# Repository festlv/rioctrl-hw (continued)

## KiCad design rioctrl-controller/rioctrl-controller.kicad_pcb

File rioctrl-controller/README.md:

# rioctrl-controller

The heart of controller is Lattice ECP5-series FPGA with 25k logic cells.

It has the following inputs/outputs:

* RJ45 Ethernet interface to PC (via Wiznet W5500)
* USB TypeC for re-flashing the FPGA (using RP2040 microcontroller with [pico-dirtyJtag](https://github.com/phdussud/pico-dirtyJtag) firmware)
* 12-24V DC input for powering the FPGA and basic slot hardware
* E-Stop signal that inhibits slot outputs in hardware, independant of FPGA gateware
* PMOD header for future expansion (e.g. controlling the board via SPI from RaspberryPi or something)
* JTAG header for FPGA debugging
* SWD header for JTAG probe debugging :)
* Six 2x13 pin 2.54mm sockets for slots (each has 12 FPGA signals, additional shared enable signal, +3.3V, +5V and input DC power)

Slot specification:
* Preferred slot PCB size: 100x100mm
* There are 12 FPGA signals wired to each slot, all of them are 3.3V.
* The following power rails are wired to each slot:
  * 3.3V
  * 5V
  * Input DC (12-24V)
* Each slot has an enable signal, whose state is a logical AND of FPGA enable output (watchdog-protected when using riocore) and external EStop input.
* Each slot **MUST** inhibit it's outputs in hardware when the enable signal is low.

# Changelog

## V1.0 -> V1.1
* Fix Y1 orientation
* DNP the USB VBUS -> 5V diode (it's useless, as 3.3V rails are generated by input voltage)
* Change LED:OK to green
 
# Bringup notes

* Build and flash the default configuration of pico-dirtyJtag (hold the boot button while turning on 12V power, then connect USB and flash via copying .uf2 to removable drive).
* Try to see if the FPGA is detected:
```
$ openFPGALoader -c dirtyJtag --detect

Jtag frequency : requested 6000000Hz -> real 6000000Hz
index 0:
	idcode 0x41111043
	manufacturer lattice
	family ECP5
	model  LFE5U-25
	irlength 8
```

# Version 1.0 rework
* Y1 needs to be rotated 90 degrees (again, sigh)
* Remove the D9 diode (USB power does not work anyway)
* Change D12 to green LED

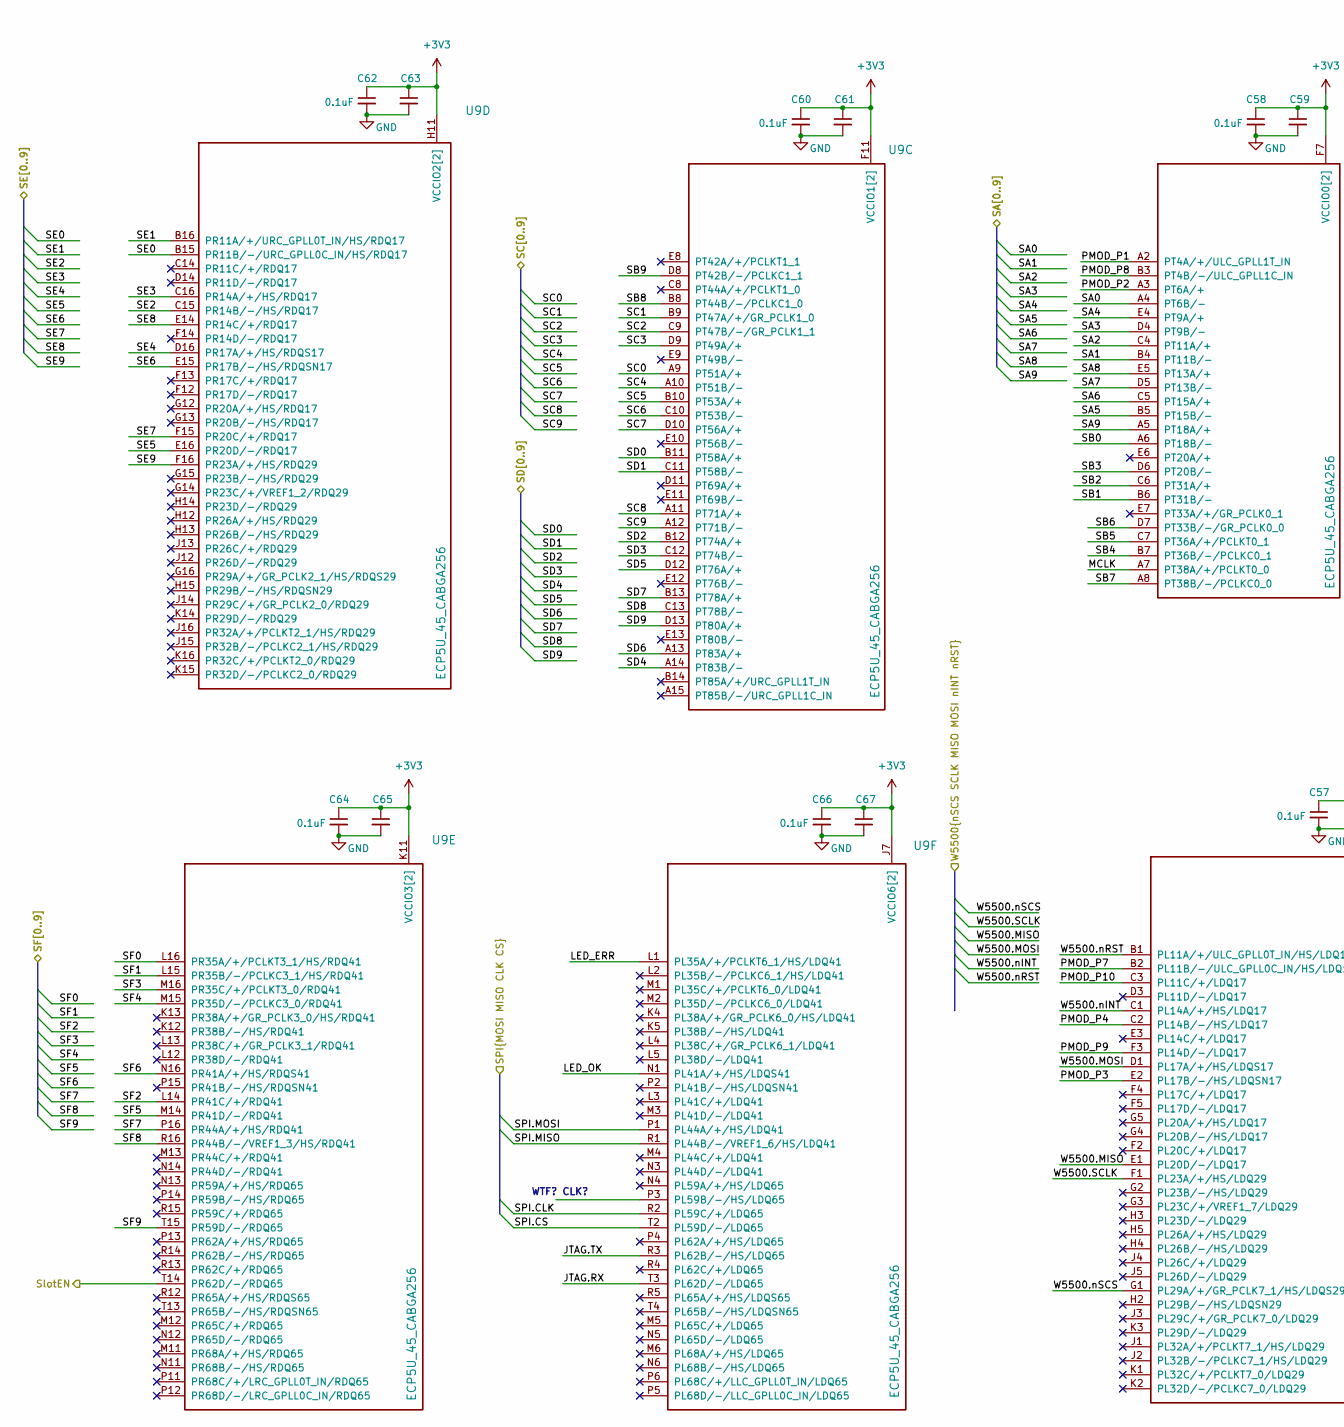
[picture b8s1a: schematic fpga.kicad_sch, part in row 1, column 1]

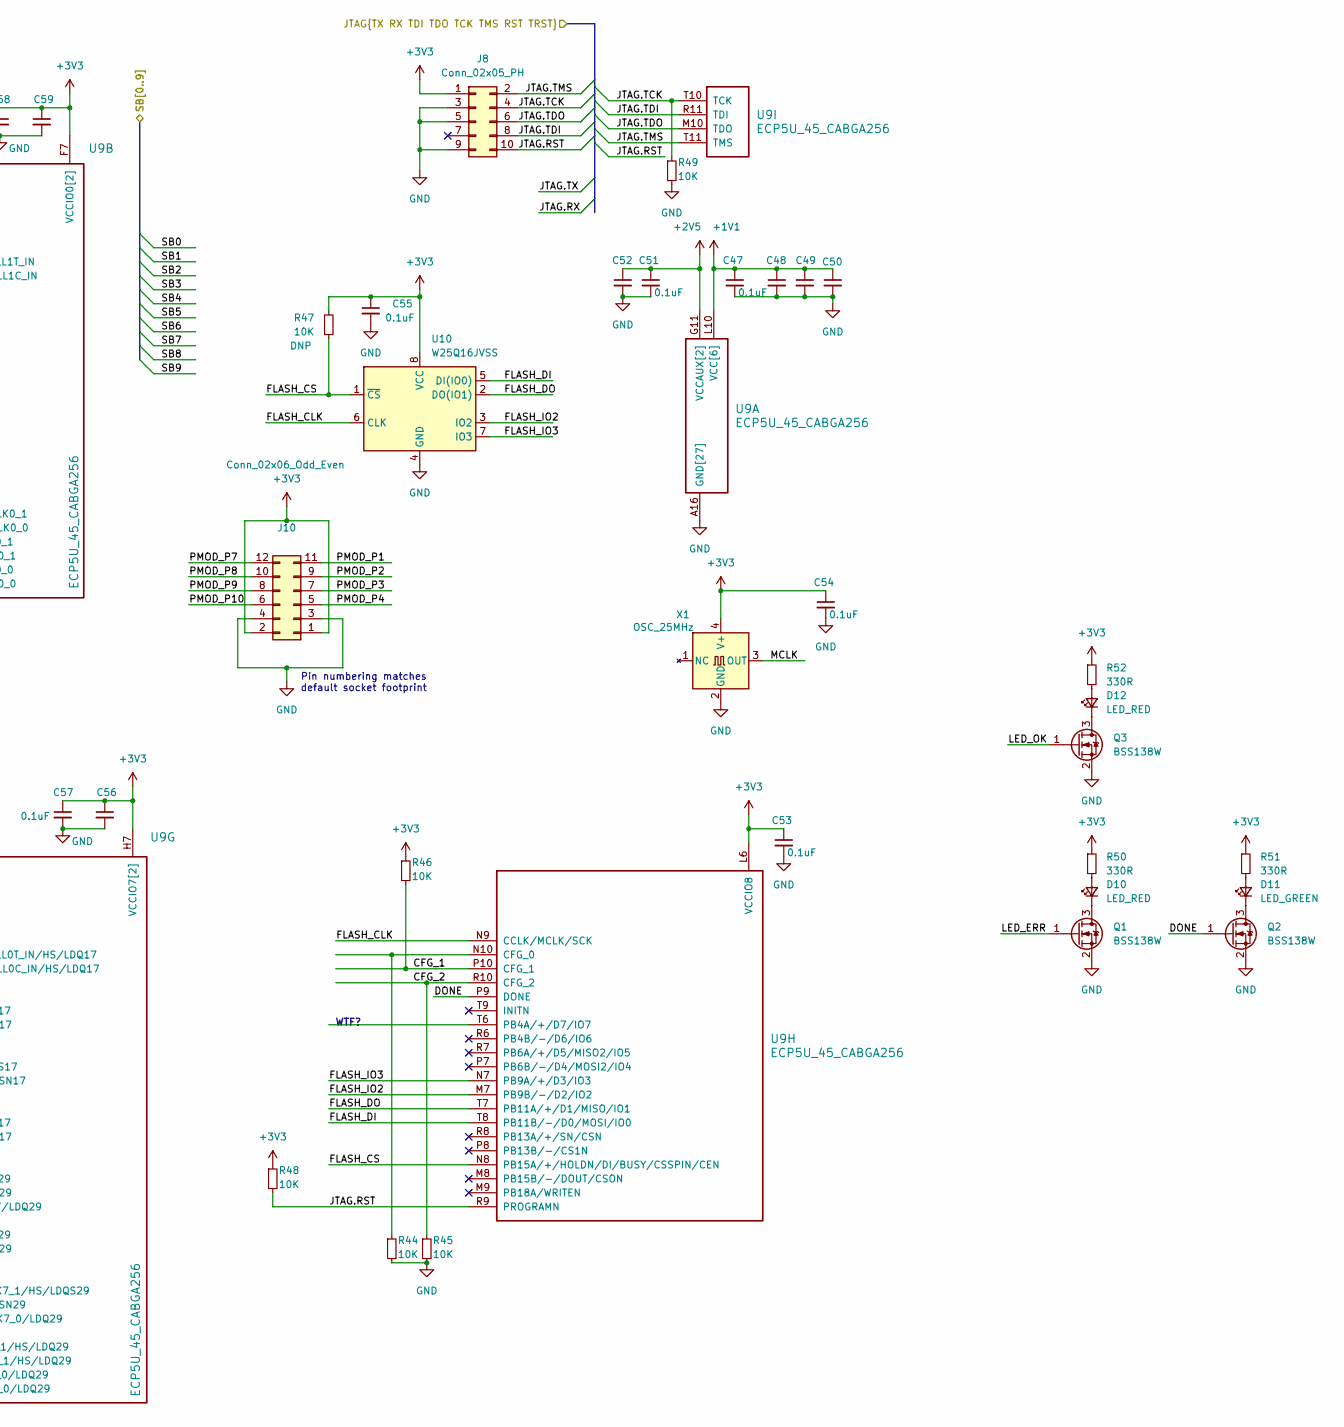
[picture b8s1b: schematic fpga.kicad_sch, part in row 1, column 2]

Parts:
C47, C48, C49, C50, C51, C52, C53, C54, C56, C57, C58, C59, C60, C61, C62, C63, C64, C65, C66, C67: 0.1uF; C_0402_1005Metric
C55: 0.1uF; C_0603_1608Metric; MPN CC0603KRX7R9BB104; LCSC# C14663
D10, D12: LED_RED; LED_0603_1608Metric; MPN SZYY0603R; LCSC# C434419
D11: LED_GREEN; LED_0603_1608Metric; MPN SZYY0603YG; LCSC# C434423
J8: Conn_02x05_PH; IDC-Header_2x05_P2.54mm_Vertical
J10: Conn_02x06_Odd_Even; PinSocket_2x06_P2.54mm_Horizontal
Q1, Q2, Q3: BSS138W; SOT-323_SC-70; MPN BSS138W; LCSC# C504052
R44, R45, R46, R48, R49: 10K; R_0603_1608Metric
R47: 10K; R_0603_1608Metric; MPN RC0603FR-0710KL; LCSC# C98220
R50, R51, R52: 330R; R_0603_1608Metric
U9: ECP5U_45_CABGA256; BGA-256_14.0x14.0mm_Layout16x16_P0.8mm_Ball0.45mm_Pad0.32mm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; MPN LFE5U-12F-6BG256C
U10: W25Q16JVSS; SOIC-8_5.23x5.23mm_P1.27mm; MPN W25Q16JVSSIQ; LCSC# C82317
X1: OSC_25MHz; Oscillator_SMD_EuroQuartz_XO32-4Pin_3.2x2.5mm; MPN OT322525MJBA4SL; LCSC# C669088

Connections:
+1V1: C47.1, C48.1, C49.1, C50.1, U9.G6 (VCC[6]), U9.G7 (VCC[6]), U9.G9 (VCC[6]), U9.L8 (VCC[6]), U9.L9 (VCC[6]), U9.L10 (VCC[6]); also elsewhere on the board
+2V5: C51.1, C52.1, U9.G11 (VCCAUX[2]), U9.L7 (VCCAUX[2]); also elsewhere on the board
+3V3: C53.1, C54.1, C55.1, C56.1, C57.1, C58.1, C59.1, C60.1, C61.1, C62.1, C63.1, C64.1, C65.1, C66.1, C67.1, J8.1, J10.1, J10.2, R46.1, R47.2, R48.1, R50.1, R51.1, R52.1, U9.F6 (VCCIO0[2]), U9.F7 (VCCIO0[2]), U9.F10 (VCCIO1[2]), U9.F11 (VCCIO1[2]), U9.H6 (VCCIO7[2]), U9.H7 (VCCIO7[2]), U9.H11 (VCCIO2[2]), U9.J6 (VCCIO6[2]), U9.J7 (VCCIO6[2]), U9.J11 (VCCIO2[2]), U9.K11 (VCCIO3[2]), U9.L6 (VCCIO8), U9.L11 (VCCIO3[2]), U10.8 (VCC), X1.4 (V+); also elsewhere on the board
/FPGA/CFG_1: R46.2, U9.P10 (CFG_1)
/FPGA/CFG_2: R45.1, U9.R10 (CFG_2)
/FPGA/DONE: Q2.1 (G), U9.P9 (DONE)
/FPGA/FLASH_CLK: U9.N9 (CCLK/MCLK/SCK), U10.6 (CLK)
/FPGA/FLASH_CS: R47.1, U9.N8 (PB15A/+/HOLDN/DI/BUSY/CSSPIN/CEN), U10.1 (~CS)
/FPGA/FLASH_DI: U9.T8 (PB11B/-/D0/MOSI/IO0), U10.5 (DI(IO0))
/FPGA/FLASH_DO: U9.T7 (PB11A/+/D1/MISO/IO1), U10.2 (DO(IO1))
/FPGA/FLASH_IO2: U9.M7 (PB9B/-/D2/IO2), U10.3 (IO2)
/FPGA/FLASH_IO3: U9.N7 (PB9A/+/D3/IO3), U10.7 (IO3)
/FPGA/LED_ERR: Q1.1 (G), U9.L1 (PL35A/+/PCLKT6_1/HS/LDQ41)
/FPGA/LED_OK: Q3.1 (G), U9.N1 (PL41A/+/HS/LDQS41)
/FPGA/MCLK: U9.A7 (PT38A/+/PCLKT0_0), X1.3 (OUT)
/FPGA/PMOD_P1: J10.11, U9.A2 (PT4A/+/ULC_GPLL1T_IN)
/FPGA/PMOD_P2: J10.9, U9.A3 (PT6A/+)
/FPGA/PMOD_P3: J10.7, U9.E2 (PL17B/-/HS/LDQSN17)
/FPGA/PMOD_P4: J10.5, U9.C2 (PL14B/-/HS/LDQ17)
/FPGA/PMOD_P7: J10.12, U9.B2 (PL11B/-/ULC_GPLL0C_IN/HS/LDQ17)
/FPGA/PMOD_P8: J10.10, U9.B3 (PT4B/-/ULC_GPLL1C_IN)
/FPGA/PMOD_P9: J10.8, U9.F3 (PL14D/-/LDQ17)
/FPGA/PMOD_P10: J10.6, U9.C3 (PL11C/+/LDQ17)
/FPGA/SA0: U9.A4 (PT6B/-); also elsewhere on the board
/FPGA/SA1: U9.B4 (PT11B/-); also elsewhere on the board
/FPGA/SA2: U9.C4 (PT11A/+); also elsewhere on the board
/FPGA/SA3: U9.D4 (PT9B/-); also elsewhere on the board
/FPGA/SA4: U9.E4 (PT9A/+); also elsewhere on the board
/FPGA/SA5: U9.B5 (PT15B/-); also elsewhere on the board
/FPGA/SA6: U9.C5 (PT15A/+); also elsewhere on the board
/FPGA/SA7: U9.D5 (PT13B/-); also elsewhere on the board
/FPGA/SA8: U9.E5 (PT13A/+); also elsewhere on the board
/FPGA/SA9: U9.A5 (PT18A/+); also elsewhere on the board
/FPGA/SB0: U9.A6 (PT18B/-); also elsewhere on the board
/FPGA/SB1: U9.B6 (PT31B/-); also elsewhere on the board
/FPGA/SB2: U9.C6 (PT31A/+); also elsewhere on the board
/FPGA/SB3: U9.D6 (PT20B/-); also elsewhere on the board
/FPGA/SB4: U9.B7 (PT36B/-/PCLKC0_1); also elsewhere on the board
/FPGA/SB5: U9.C7 (PT36A/+/PCLKT0_1); also elsewhere on the board
/FPGA/SB6: U9.D7 (PT33B/-/GR_PCLK0_0); also elsewhere on the board
/FPGA/SB7: U9.A8 (PT38B/-/PCLKC0_0); also elsewhere on the board
/FPGA/SB8: U9.B8 (PT44B/-/PCLKC1_0); also elsewhere on the board
/FPGA/SB9: U9.D8 (PT42B/-/PCLKC1_1); also elsewhere on the board
/FPGA/SC0: U9.A9 (PT51A/+); also elsewhere on the board
/FPGA/SC1: U9.B9 (PT47A/+/GR_PCLK1_0); also elsewhere on the board
/FPGA/SC2: U9.C9 (PT47B/-/GR_PCLK1_1); also elsewhere on the board
/FPGA/SC3: U9.D9 (PT49A/+); also elsewhere on the board
/FPGA/SC4: U9.A10 (PT51B/-); also elsewhere on the board
/FPGA/SC5: U9.B10 (PT53A/+); also elsewhere on the board
/FPGA/SC6: U9.C10 (PT53B/-); also elsewhere on the board
/FPGA/SC7: U9.D10 (PT56A/+); also elsewhere on the board
/FPGA/SC8: U9.A11 (PT71A/+); also elsewhere on the board
/FPGA/SC9: U9.A12 (PT71B/-); also elsewhere on the board
/FPGA/SD0: U9.B11 (PT58A/+); also elsewhere on the board
/FPGA/SD1: U9.C11 (PT58B/-); also elsewhere on the board
/FPGA/SD2: U9.B12 (PT74A/+); also elsewhere on the board
/FPGA/SD3: U9.C12 (PT74B/-); also elsewhere on the board
/FPGA/SD4: U9.A14 (PT83B/-); also elsewhere on the board
/FPGA/SD5: U9.D12 (PT76A/+); also elsewhere on the board
/FPGA/SD6: U9.A13 (PT83A/+); also elsewhere on the board
/FPGA/SD7: U9.B13 (PT78A/+); also elsewhere on the board
/FPGA/SD8: U9.C13 (PT78B/-); also elsewhere on the board
/FPGA/SD9: U9.D13 (PT80A/+); also elsewhere on the board
/FPGA/SE0: U9.B15 (PR11B/-/URC_GPLL0C_IN/HS/RDQ17); also elsewhere on the board
/FPGA/SE1: U9.B16 (PR11A/+/URC_GPLL0T_IN/HS/RDQ17); also elsewhere on the board
/FPGA/SE2: U9.C15 (PR14B/-/HS/RDQ17); also elsewhere on the board
/FPGA/SE3: U9.C16 (PR14A/+/HS/RDQ17); also elsewhere on the board
/FPGA/SE4: U9.D16 (PR17A/+/HS/RDQS17); also elsewhere on the board
/FPGA/SE5: U9.E16 (PR20D/-/RDQ17); also elsewhere on the board
/FPGA/SE6: U9.E15 (PR17B/-/HS/RDQSN17); also elsewhere on the board
/FPGA/SE7: U9.F15 (PR20C/+/RDQ17); also elsewhere on the board
/FPGA/SE8: U9.E14 (PR14C/+/RDQ17); also elsewhere on the board
/FPGA/SE9: U9.F16 (PR23A/+/HS/RDQ29); also elsewhere on the board
/FPGA/SF0: U9.L16 (PR35A/+/PCLKT3_1/HS/RDQ41); also elsewhere on the board
/FPGA/SF1: U9.L15 (PR35B/-/PCLKC3_1/HS/RDQ41); also elsewhere on the board
/FPGA/SF2: U9.L14 (PR41C/+/RDQ41); also elsewhere on the board
/FPGA/SF3: U9.M16 (PR35C/+/PCLKT3_0/RDQ41); also elsewhere on the board
/FPGA/SF4: U9.M15 (PR35D/-/PCLKC3_0/RDQ41); also elsewhere on the board
/FPGA/SF5: U9.M14 (PR41D/-/RDQ41); also elsewhere on the board
/FPGA/SF6: U9.N16 (PR41A/+/HS/RDQS41); also elsewhere on the board
/FPGA/SF7: U9.P16 (PR44A/+/HS/RDQ41); also elsewhere on the board
/FPGA/SF8: U9.R16 (PR44B/-/VREF1_3/HS/RDQ41); also elsewhere on the board
/FPGA/SF9: U9.T15 (PR59D/-/RDQ65); also elsewhere on the board
/FPGA/SPI.CLK: U9.R2 (PL59C/+/LDQ65); also elsewhere on the board
/FPGA/SPI.CS: U9.T2 (PL59D/-/LDQ65); also elsewhere on the board
/FPGA/SPI.MISO: U9.R1 (PL44B/-/VREF1_6/HS/LDQ41); also elsewhere on the board
/FPGA/SPI.MOSI: U9.P1 (PL44A/+/HS/LDQ41); also elsewhere on the board
/FPGA/W5500.MISO: U9.E1 (PL20D/-/LDQ17); also elsewhere on the board
/FPGA/W5500.MOSI: U9.D1 (PL17A/+/HS/LDQS17); also elsewhere on the board
/FPGA/W5500.SCLK: U9.F1 (PL23A/+/HS/LDQ29); also elsewhere on the board
/FPGA/W5500.nINT: U9.C1 (PL14A/+/HS/LDQ17); also elsewhere on the board
/FPGA/W5500.nRST: U9.B1 (PL11A/+/ULC_GPLL0T_IN/HS/LDQ17); also elsewhere on the board
/FPGA/W5500.nSCS: U9.G1 (PL29A/+/GR_PCLK7_1/HS/LDQS29); also elsewhere on the board
/RP2040 JTAG/JTAG.RST: J8.10, R48.2, U9.R9 (PROGRAMN); also elsewhere on the board
/RP2040 JTAG/JTAG.RX: U9.T3 (PL62D/-/LDQ65); also elsewhere on the board
/RP2040 JTAG/JTAG.TCK: J8.4, R49.1, U9.T10 (TCK); also elsewhere on the board
/RP2040 JTAG/JTAG.TDI: J8.8, U9.R11 (TDI); also elsewhere on the board
/RP2040 JTAG/JTAG.TDO: J8.6, U9.M10 (TDO); also elsewhere on the board
/RP2040 JTAG/JTAG.TMS: J8.2, U9.T11 (TMS); also elsewhere on the board
/RP2040 JTAG/JTAG.TX: U9.R3 (PL62B/-/HS/LDQ65); also elsewhere on the board
/Slots/SlotEN: U9.T14 (PR62D/-/RDQ65); also elsewhere on the board
GND: C47.2, C48.2, C49.2, C50.2, C51.2, C52.2, C53.2, C54.2, C55.2, C56.2, C57.2, C58.2, C59.2, C60.2, C61.2, C62.2, C63.2, C64.2, C65.2, C66.2, C67.2, J8.3, J8.5, J8.9, J10.3, J10.4, Q1.2 (S), Q2.2 (S), Q3.2 (S), R44.2, R45.2, R49.2, U9.A1 (GND[27]), U9.A16 (GND[27]), U9.D2 (GND[27]), U9.D15 (GND[27]), U9.F8 (GND[27]), U9.F9 (GND[27]), U9.G8 (GND[27]), U9.G10 (GND[27]), U9.H1 (GND[27]), U9.H8 (GND[27]), U9.H9 (GND[27]), U9.H10 (GND[27]), U9.H16 (GND[27]), U9.J8 (GND[27]), U9.J9 (GND[27]), U9.J10 (GND[27]), U9.K6 (GND[27]), U9.K7 (GND[27]), U9.K8 (GND[27]), U9.K9 (GND[27]), U9.K10 (GND[27]), U9.N2 (GND[27]), U9.N15 (GND[27]), U9.T1 (GND[27]), U9.T5 (GND[27]), U9.T12 (GND[27]), U9.T16 (GND[27]), U10.4 (GND), X1.2 (GND); also elsewhere on the board
unnamed: D10.2 (A), R50.2
unnamed: D10.1 (K), Q1.3 (D)
unnamed: D11.2 (A), R51.2
unnamed: D11.1 (K), Q2.3 (D)
unnamed: D12.2 (A), R52.2
unnamed: D12.1 (K), Q3.3 (D)
unnamed: R44.1, U9.N10 (CFG_0)

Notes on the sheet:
WTF?
WTF? CLK?
Pin numbering matches default socket footprint

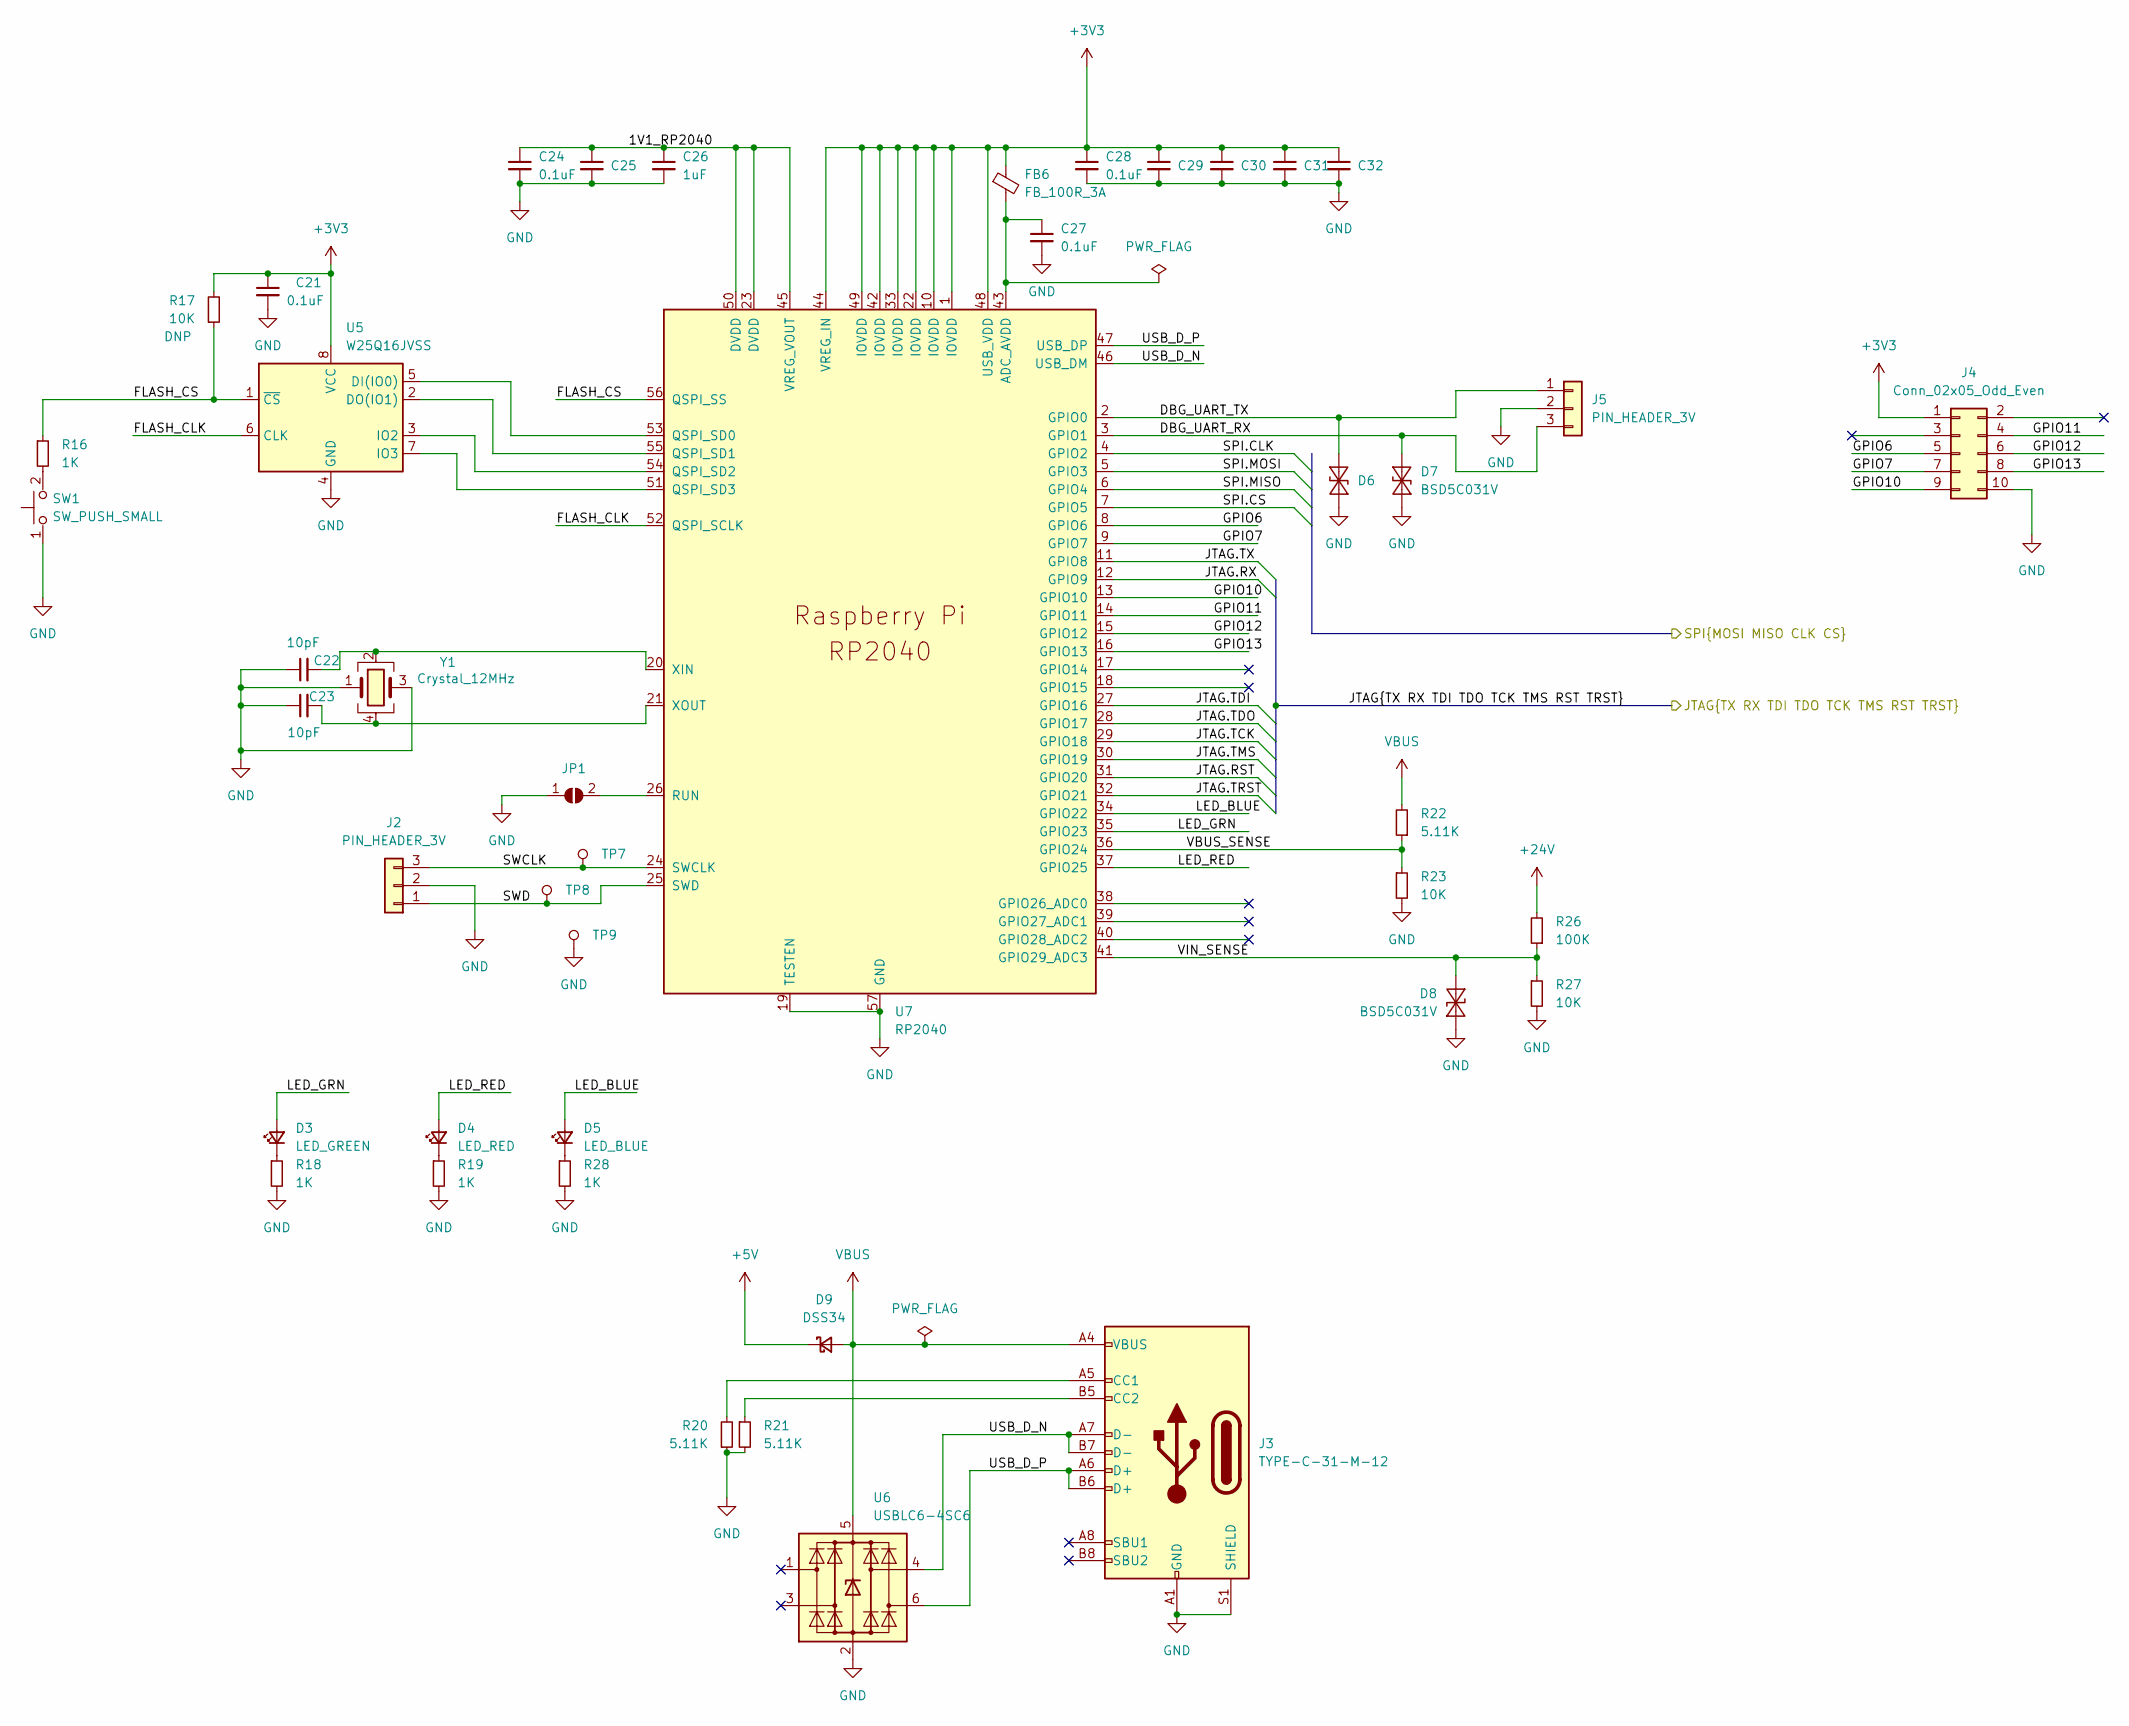
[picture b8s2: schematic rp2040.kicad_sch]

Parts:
C21, C24, C25, C27, C28, C29, C30, C31, C32: 0.1uF; C_0603_1608Metric; MPN CC0603KRX7R9BB104; LCSC# C14663
C22, C23: 10pF; C_0603_1608Metric; MPN CC0603JRNPO9BN100; LCSC# C106245
C26: 1uF; C_0603_1608Metric; MPN CL10A105KA8NNNC; LCSC# C5673
D3: LED_GREEN; LED_0603_1608Metric; MPN SZYY0603YG; LCSC# C434423
D4: LED_RED; LED_0603_1608Metric; MPN SZYY0603R; LCSC# C434419
D5: LED_BLUE; LED_0603_1608Metric; MPN XL-1608UBC-04; LCSC# C965807
D6, D7, D8: BSD5C031V; D_SOD-523; MPN BSD5C031V; LCSC# C151984
D9: DSS34; D_SOD-123F; MPN DSS34; LCSC# C511866
FB6: FB_100R_3A; L_0603_1608Metric; MPN UPZ1608E101-3R0TF; LCSC# C96995
J2, J5: PIN_HEADER_3V; PinHeader_1x03_P2.54mm_Vertical; MPN C49257; LCSC# C49257
J3: TYPE-C-31-M-12; USB_C_Receptacle_HRO_TYPE-C-31-M-12; MPN TYPE-C-31-M-12; LCSC# C165948
J4: Conn_02x05_Odd_Even; PinHeader_2x05_P2.54mm_Vertical
JP1: SolderJumper_2_Open; SolderJumper-2_P1.3mm_Open_RoundedPad1.0x1.5mm
R16, R18, R19, R28: 1K; R_0603_1608Metric; MPN RC0603FR-071KL; LCSC# C22548
R17, R23, R27: 10K; R_0603_1608Metric; MPN RC0603FR-0710KL; LCSC# C98220
R20, R21, R22: 5.11K; R_0603_1608Metric; MPN RC0603FR-075K11L; LCSC# C112314
R26: 100K; R_0603_1608Metric; MPN RC0603FR-075K11L; LCSC# C112314
SW1: SW_PUSH_SMALL; SW_SPST_AR02016; MPN TS-1088-AR02016; LCSC# C720477
TP7, TP8, TP9: TP_1MM; TestPoint_Pad_D1.0mm
U5: W25Q16JVSS; SOIC-8_5.23x5.23mm_P1.27mm; MPN W25Q16JVSSIQ; LCSC# C82317
U6: USBLC6-4SC6; SOT-23-6; MPN USBLC6-4SC6; LCSC# C5197386
U7: RP2040; RP2040-QFN-56; MPN RP2040; LCSC# C2040
Y1: Crystal_12MHz; Crystal_SMD_2520-4Pin_2.5x2.0mm; MPN TXM12M0004252DBCEO00T; LCSC# C284154

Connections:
+3V3: C21.1, C28.1, C29.1, C30.1, C31.1, C32.1, FB6.1, J4.1, R17.2, U5.8 (VCC), U7.1 (IOVDD), U7.10 (IOVDD), U7.22 (IOVDD), U7.33 (IOVDD), U7.42 (IOVDD), U7.44 (VREG_IN), U7.48 (USB_VDD), U7.49 (IOVDD); also elsewhere on the board
+5V: D9.1 (K); also elsewhere on the board
+24V: R26.2; also elsewhere on the board
/FPGA/SPI.CLK: U7.4 (GPIO2); also elsewhere on the board
/FPGA/SPI.CS: U7.7 (GPIO5); also elsewhere on the board
/FPGA/SPI.MISO: U7.6 (GPIO4); also elsewhere on the board
/FPGA/SPI.MOSI: U7.5 (GPIO3); also elsewhere on the board
/RP2040 JTAG/1V1_RP2040: C24.1, C25.1, C26.1, U7.23 (DVDD), U7.45 (VREG_VOUT), U7.50 (DVDD)
/RP2040 JTAG/DBG_UART_RX: D7.2 (A2), J5.3, U7.3 (GPIO1)
/RP2040 JTAG/DBG_UART_TX: D6.2 (A2), J5.1, U7.2 (GPIO0)
/RP2040 JTAG/FLASH_CLK: U5.6 (CLK), U7.52 (QSPI_SCLK)
/RP2040 JTAG/FLASH_CS: R16.1, R17.1, U5.1 (~CS), U7.56 (QSPI_SS)
/RP2040 JTAG/GPIO6: J4.5, U7.8 (GPIO6)
/RP2040 JTAG/GPIO7: J4.7, U7.9 (GPIO7)
/RP2040 JTAG/GPIO10: J4.9, U7.13 (GPIO10)
/RP2040 JTAG/GPIO11: J4.4, U7.14 (GPIO11)
/RP2040 JTAG/GPIO12: J4.6, U7.15 (GPIO12)
/RP2040 JTAG/GPIO13: J4.8, U7.16 (GPIO13)
/RP2040 JTAG/JTAG.RST: U7.31 (GPIO20); also elsewhere on the board
/RP2040 JTAG/JTAG.RX: U7.12 (GPIO9); also elsewhere on the board
/RP2040 JTAG/JTAG.TCK: U7.29 (GPIO18); also elsewhere on the board
/RP2040 JTAG/JTAG.TDI: U7.27 (GPIO16); also elsewhere on the board
/RP2040 JTAG/JTAG.TDO: U7.28 (GPIO17); also elsewhere on the board
/RP2040 JTAG/JTAG.TMS: U7.30 (GPIO19); also elsewhere on the board
/RP2040 JTAG/JTAG.TRST: U7.32 (GPIO21)
/RP2040 JTAG/JTAG.TX: U7.11 (GPIO8); also elsewhere on the board
/RP2040 JTAG/LED_BLUE: D5.2 (A), U7.34 (GPIO22)
/RP2040 JTAG/LED_GRN: D3.2 (A), U7.35 (GPIO23)
/RP2040 JTAG/LED_RED: D4.2 (A), U7.37 (GPIO25)
/RP2040 JTAG/SWCLK: J2.3, TP7.1, U7.24 (SWCLK)
/RP2040 JTAG/SWD: J2.1, TP8.1, U7.25 (SWD)
/RP2040 JTAG/USB_D_N: J3.A7 (D-), J3.B7 (D-), U6.4 (I/O3), U7.46 (USB_DM)
/RP2040 JTAG/USB_D_P: J3.A6 (D+), J3.B6 (D+), U6.6 (I/O4), U7.47 (USB_DP)
/RP2040 JTAG/VBUS_SENSE: R22.1, R23.1, U7.36 (GPIO24)
/RP2040 JTAG/VIN_SENSE: D8.2 (A2), R26.1, R27.1, U7.41 (GPIO29_ADC3)
GND: C21.2, C22.1, C23.1, C24.2, C25.2, C26.2, C27.2, C28.2, C29.2, C30.2, C31.2, C32.2, D6.1 (A1), D7.1 (A1), D8.1 (A1), J2.2, J3.A1 (GND), J3.A12 (GND), J3.B1 (GND), J3.B12 (GND), J3.S1 (SHIELD), J4.10, J5.2, JP1.1 (A), R18.2, R19.2, R20.1, R21.2, R23.2, R27.2, R28.2, SW1.1, TP9.1, U5.4 (GND), U6.2 (GND), U7.19 (TESTEN), U7.57 (GND), Y1.1, Y1.3; also elsewhere on the board
unnamed: D3.1 (K), R18.1
unnamed: D4.1 (K), R19.1
unnamed: D5.1 (K), R28.1
unnamed: J3.A5 (CC1), R20.2
unnamed: J3.B5 (CC2), R21.1
unnamed: JP1.2 (B), U7.26 (RUN)
unnamed: R16.2, SW1.2 (A)
unnamed: U5.5 (DI(IO0)), U7.53 (QSPI_SD0)
unnamed: U5.2 (DO(IO1)), U7.55 (QSPI_SD1)
unnamed: U5.3 (IO2), U7.54 (QSPI_SD2)
unnamed: U5.7 (IO3), U7.51 (QSPI_SD3)
unnamed: C27.1, FB6.2, U7.43 (ADC_AVDD)
unnamed: C22.2, U7.20 (XIN), Y1.2
unnamed: C23.2, U7.21 (XOUT), Y1.4
VBUS: D9.2 (A), J3.A4 (VBUS), J3.A9 (VBUS), J3.B4 (VBUS), J3.B9 (VBUS), R22.2, U6.5 (VBUS)

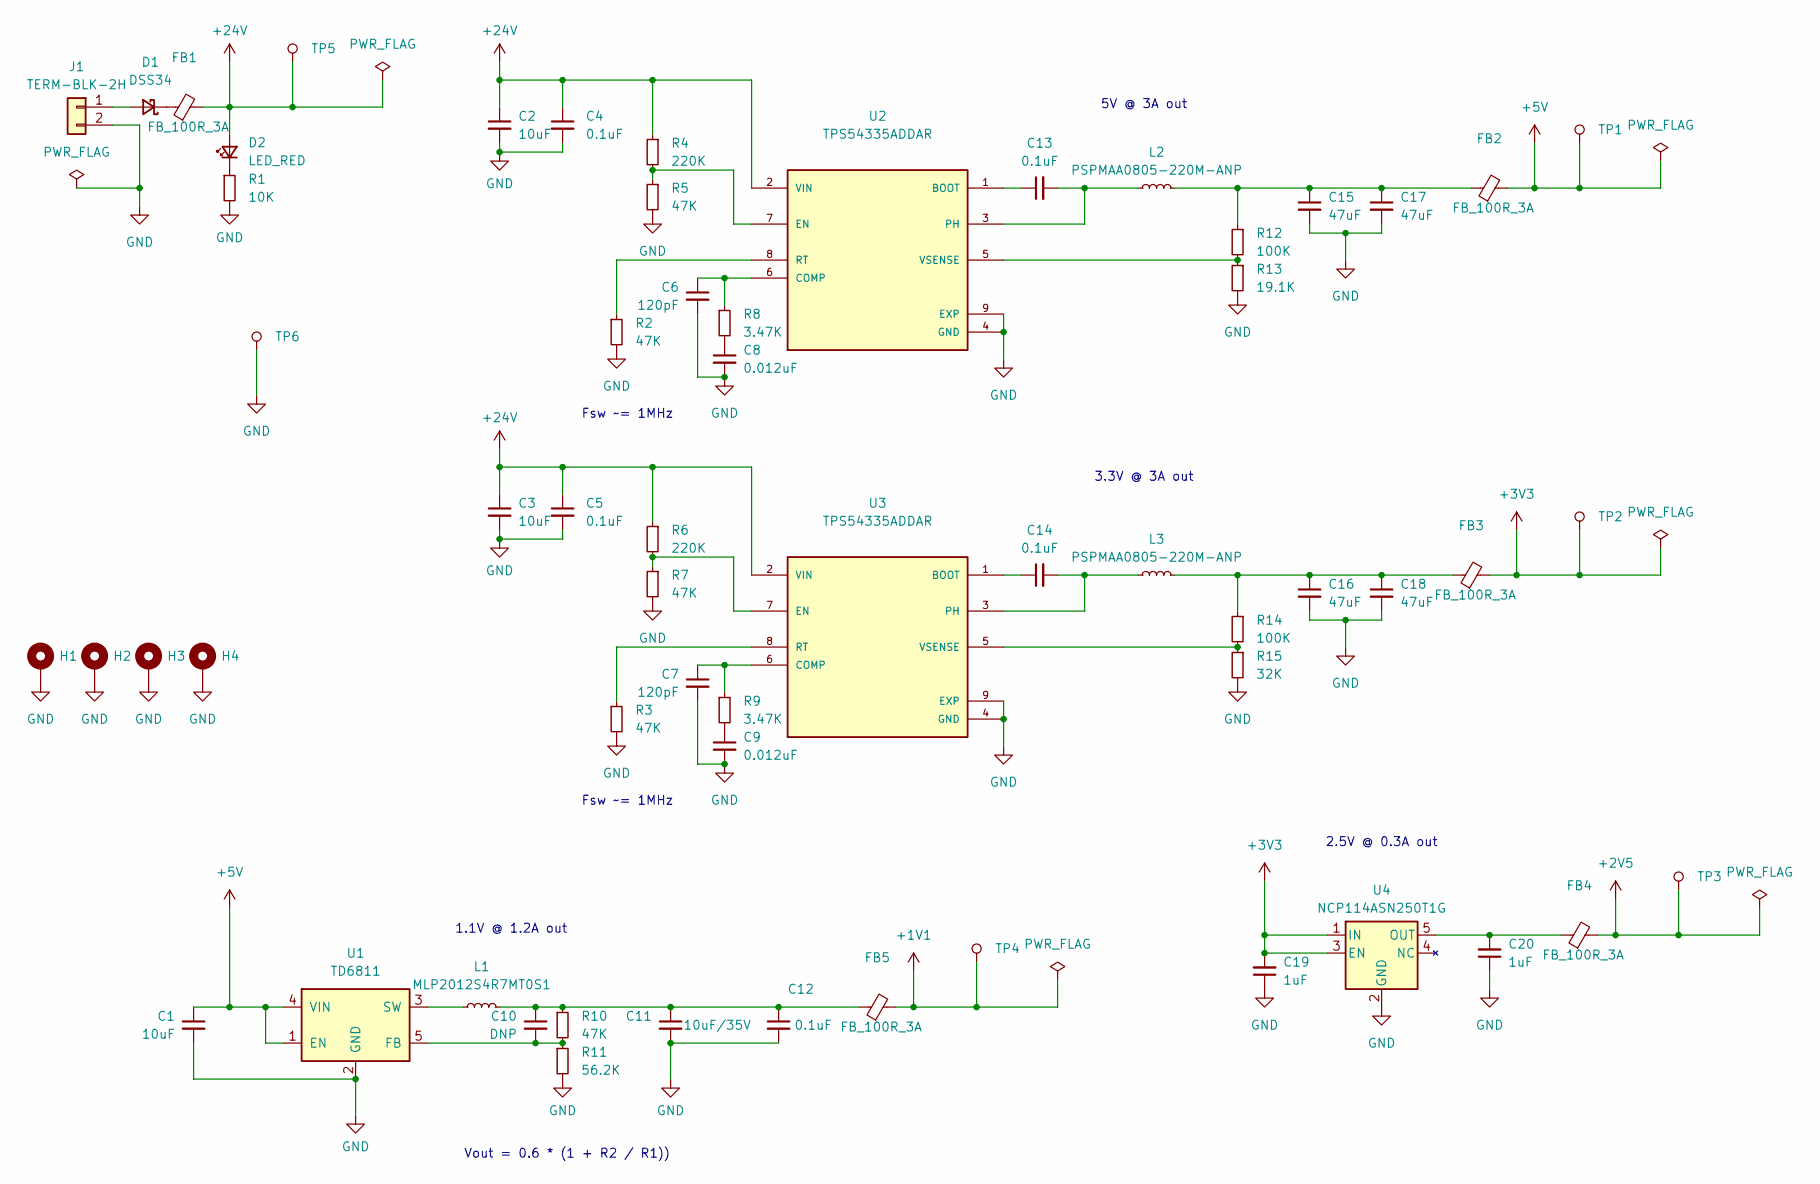
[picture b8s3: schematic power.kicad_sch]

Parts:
C1: 10uF; C_0805_2012Metric; MPN GRM21BR6YA106ME43L; LCSC# C361063
C2, C3: 10uF; C_0805_2012Metric; MPN GRM21BR61H106KE43L; LCSC# C440198
C4, C5, C13, C14: 0.1uF; C_0603_1608Metric
C6, C7: 120pF; C_0603_1608Metric
C8, C9: 0.012uF; C_0603_1608Metric
C10: DNP; C_0603_1608Metric
C11: 10uF/35V; C_0805_2012Metric; MPN GRM21BR6YA106ME43L; LCSC# C361063
C12: 0.1uF; C_0603_1608Metric; MPN CC0603KRX7R9BB104; LCSC# C14663
C15, C16, C17, C18: 47uF; C_0805_2012Metric; MPN GRM21BR61H106KE43L; LCSC# C440198
C19, C20: 1uF; C_0603_1608Metric
D1: DSS34; D_SOD-123F; MPN DSS34; LCSC# C511866
D2: LED_RED; LED_0603_1608Metric; MPN SZYY0603R; LCSC# C434419
FB1, FB2, FB3, FB4, FB5: FB_100R_3A; L_0603_1608Metric; MPN UPZ1608E101-3R0TF; LCSC# C96995
H1, H2, H3, H4: MH_3.2mm; MountingHole_3.2mm_M3_Pad_Via
J1: TERM-BLK-2H; PhoenixContact_MC_1,5_2-G-3.5_1x02_P3.50mm_Horizontal; MPN KF2EDGR-3.5-2P; LCSC# C441171
L1: MLP2012S4R7MT0S1; L_0805_2012Metric; MPN MLP2012S4R7MT0S1; LCSC# C87543
L2, L3: PSPMAA0805-220M-ANP; SMD_INDUCTOR_8x8.5x5mm; MPN PSPMAA0805-220M-ANP; LCSC# C2962887
R1: 10K; R_0603_1608Metric
R2, R3, R5, R7, R10: 47K; R_0603_1608Metric
R4, R6: 220K; R_0603_1608Metric
R8, R9: 3.47K; R_0603_1608Metric
R11: 56.2K; R_0603_1608Metric; MPN RC0603FR-0710KL; LCSC# C98220
R12, R14: 100K; R_0603_1608Metric
R13: 19.1K; R_0603_1608Metric
R15: 32K; R_0603_1608Metric
TP1, TP2, TP3, TP4, TP5, TP6: TP_1MM; TestPoint_Pad_D1.0mm
U1: TD6811; SOT-23-5; MPN TD6811; LCSC# C189486
U2, U3: TPS54335ADDAR; SOIC-8-1EP_3.9x4.9mm_P1.27mm_EP2.29x3mm_ThermalVias; MPN TPS54335ADDAR; LCSC# C58928
U4: NCP114ASN250T1G; SOT-23-5; MPN NCP114ASN250T1G; LCSC# C892030

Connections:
+1V1: FB5.2, TP4.1; also elsewhere on the board
+2V5: FB4.2, TP3.1; also elsewhere on the board
+3V3: C19.2, FB3.2, TP2.1, U4.1 (IN), U4.3 (EN); also elsewhere on the board
+5V: C1.1, FB2.2, TP1.1, U1.1 (EN), U1.4 (VIN); also elsewhere on the board
+24V: C2.1, C3.1, C4.1, C5.1, D2.2 (A), FB1.2, R4.1, R6.1, TP5.1, U2.2 (VIN), U3.2 (VIN); also elsewhere on the board
GND: C1.2, C2.2, C3.2, C4.2, C5.2, C6.2, C7.2, C8.2, C9.2, C11.2, C12.2, C15.2, C16.2, C17.2, C18.2, C19.1, C20.1, H1.1, H2.1, H3.1, H4.1, J1.2, R1.2, R2.2, R3.2, R5.2, R7.2, R11.2, R13.2, R15.2, TP6.1, U1.2 (GND), U2.4 (GND), U2.9 (EXP), U3.4 (GND), U3.9 (EXP), U4.2 (GND); also elsewhere on the board
unnamed: C8.1, R8.2
unnamed: C9.1, R9.2
unnamed: C10.1, C11.1, C12.1, FB5.1, L1.2, R10.1
unnamed: C15.1, C17.1, FB2.1, L2.2, R12.1
unnamed: C16.1, C18.1, FB3.1, L3.2, R14.1
unnamed: D1.2 (A), J1.1
unnamed: D1.1 (K), FB1.1
unnamed: D2.1 (K), R1.1
unnamed: C10.2, R10.2, R11.1, U1.5 (FB)
unnamed: L1.1, U1.3 (SW)
unnamed: C13.1, U2.1 (BOOT)
unnamed: C6.1, R8.1, U2.6 (COMP)
unnamed: R4.2, R5.1, U2.7 (EN)
unnamed: C13.2, L2.1, U2.3 (PH)
unnamed: R2.1, U2.8 (RT)
unnamed: R12.2, R13.1, U2.5 (VSENSE)
unnamed: C14.1, U3.1 (BOOT)
unnamed: C7.1, R9.1, U3.6 (COMP)
unnamed: R6.2, R7.1, U3.7 (EN)
unnamed: C14.2, L3.1, U3.3 (PH)
unnamed: R3.1, U3.8 (RT)
unnamed: R14.2, R15.1, U3.5 (VSENSE)
unnamed: C20.2, FB4.1, U4.5 (OUT)

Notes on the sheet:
1.1V @ 1.2A out
Fsw ~= 1MHz
Vout = 0.6 * (1 + R2 / R1))
3.3V @ 3A out
5V @ 3A out
2.5V @ 0.3A out
